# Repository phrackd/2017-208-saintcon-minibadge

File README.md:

SAINTCON 2017 208 Mini Badge
===
AtTiny13A charlieplexed 18 leds (5 pins).

LED 1-18 (Red)
http://www.mouser.com/ProductDetail/VCC/CMDA6BR7D1S-100/?qs=sGAEpiMZZMseGfSY3csMkcsbWSsnAeSJ68pK%2f0XFmBo%3d

LED 1-18 (Blue)
http://www.mouser.com/ProductDetail/Inolux-Harvatek/HT-193NB-5589/?qs=sGAEpiMZZMseGfSY3csMkc1HPTPU%252bBvkJGeVXRsZXqY%3d

U1
http://www.mouser.com/ProductDetail/Microchip-Technology-Atmel/ATTINY13A-SSH/?qs=sGAEpiMZZMu9ReDVvI6ax12j%2fmgQXOIbML48wDlliyg%3d

C1
http://www.mouser.com/ProductDetail/AVX/06033C104K4T4A/?qs=sGAEpiMZZMs0AnBnWHyRQCvwBt31FSTBNcopTn8bDD4%3d

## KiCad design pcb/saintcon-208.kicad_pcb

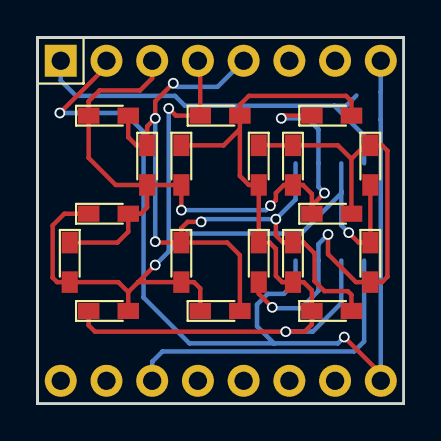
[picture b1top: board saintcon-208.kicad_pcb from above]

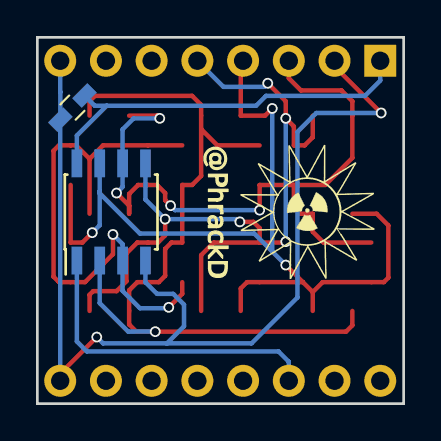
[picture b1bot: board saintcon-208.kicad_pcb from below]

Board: 2 copper layers, 20.3 x 20.3 mm, 22 parts (3 on the bottom side), 8 nets.

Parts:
C1: C; C_0603_HandSoldering
D1, D2, D3, D4, D5, D6, D7, D8, D9, D10, D11, D12, D13, D14, D15, D16, D17, D18: LED; LED_0603_HandSoldering
M1: BADGE64FOOTPRINT; MiniBadge-BADGE64-FOOTPRINT
U1: ATTINY13-20SSU; SOIC-8_3.9x4.9mm_Pitch1.27mm
img: img

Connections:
unnamed: C1.1, M1.1, U1.8
unnamed: C1.2, M1.2, M1.8, M1.9, U1.4
unnamed: D1.1, D2.2, D3.2, D4.1, D11.2, D12.1, D17.2, D18.1, M1.3, U1.6
unnamed: D1.2, D2.1, D9.2, D10.1, D15.2, D16.1, M1.5, U1.5
unnamed: D3.1, D4.2, D5.2, D6.1, D9.1, D10.2, D13.2, D14.1, M1.4, U1.7
unnamed: D5.1, D6.2, D7.2, D8.1, D11.1, D12.2, D15.1, D16.2, U1.2
unnamed: D7.1, D8.2, D13.1, D14.2, D17.1, D18.2, U1.3
unnamed: M1.14, U1.1

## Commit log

2017-10-17 release
